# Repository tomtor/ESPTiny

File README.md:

# ATtiny84/16x4/x02 and ESP-01 (ESP8266) KiCad PCB and example code

## Usage

The main function of the ATtiny is acting as a battery friendly low power co-processor for the ESP.
A bit like the ULP low power co-processor of the ESP32, except with a lot more IO functions and program memory.

ATtiny and ESP combined use 22uA in sleep mode or even less when the ESP
is switched off by the ATtiny with CS.

Usable on breadboard (ATtiny84: 9 rows high, leaves 2 rows empty and ATtiny16x4: 8 rows high) OR stand alone.

3 PCB designs: ATtiny84 or ATtiny16x4 or ATtinyx02

All components / features are optional:

- ATtiny84 or ATtiny1604 / ATtiny1614 or ATtiny202 / ATtiny402
- ESP-01 (When not used the connections/space can be used for any other (I2C) device)
- LED with resistor
- MCP1700 low quiescent current regulator
- BAT85 diode for Solar Charging panel (see https://www.thethingsnetwork.org/labs/story/a-cheap-stm32-arduino-node/step/solar-power)
- Voltage divider for measuring battery voltage
- Decoupling capacitors
- I2C communication between ESP and ATtiny (with optional 4k7 pull-up)
- ATtiny can restart ESP by pulling ESP Reset low

## Example code

The ATtiny wakes up the ESP every 10 minutes by pulling RST low and sends a counter and the supply voltage to it.

### OTA for the ESP
OTA for ESP program updates is activated for 20s when the I2C communication fails.
This can be triggered by resetting the ESP by pulling the RST line low.
Because the ATtiny is most of the time sleeping
the I2C communication will fail.

There is a small chance that the ATtiny will reset the ESP during upload when the 10 minute interval is completed.
You can prevent this by pulling the ATtiny RST low when using OTA, or just upload again.

## Schemas

https://github.com/tomtor/ESPTiny/raw/master/ESPTiny.pdf

https://github.com/tomtor/ESPTiny/raw/master/ESPTiny1614.pdf

https://github.com/tomtor/ESPTiny/raw/master/ESPTiny402.pdf

## Credits

https://github.com/jdunmire/kicad-ESP8266

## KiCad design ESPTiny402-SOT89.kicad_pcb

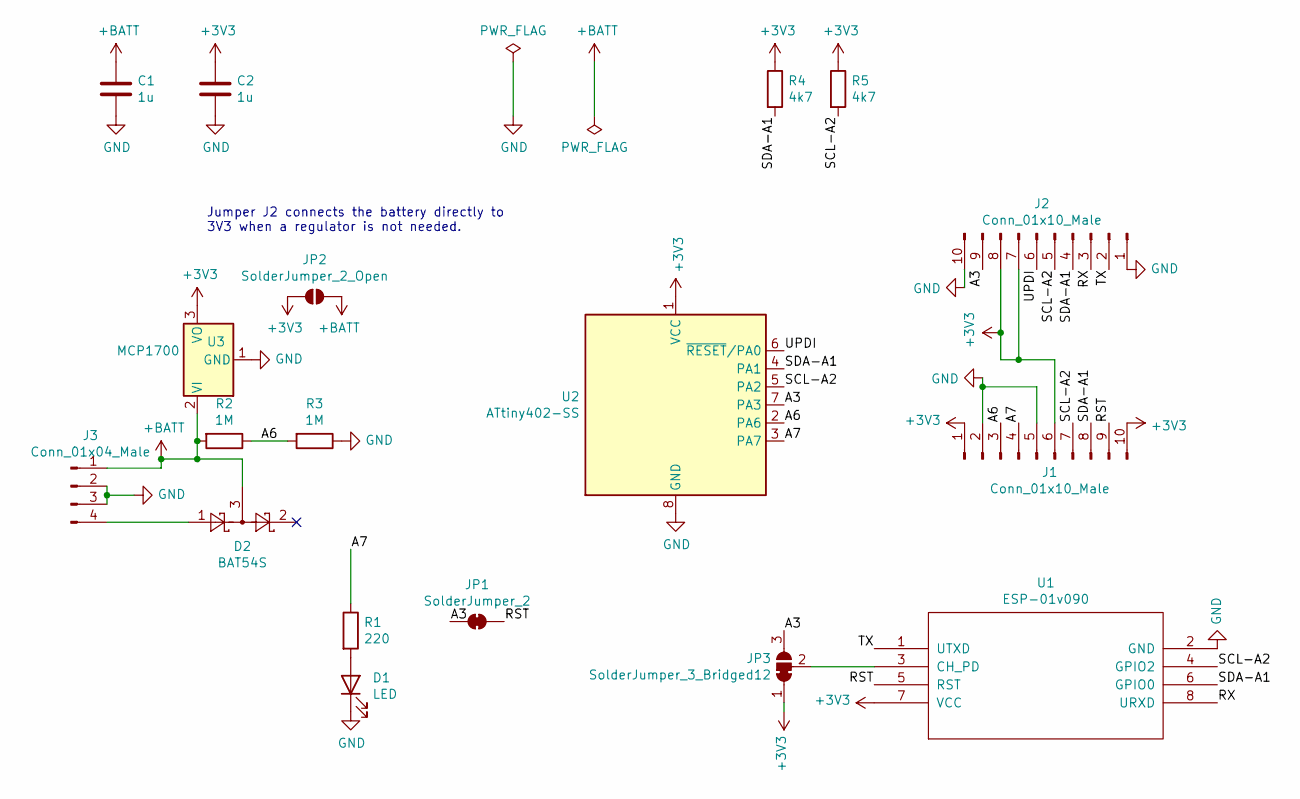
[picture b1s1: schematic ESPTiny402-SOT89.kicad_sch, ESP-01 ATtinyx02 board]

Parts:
C1, C2: 1u; C_1206_3216Metric
D1: LED; LED_1206_3216Metric
D2: BAT54S; SOT-23
J1, J2: Conn_01x10_Male; PinHeader_1x10_P2.54mm_Vertical
J3: Conn_01x04_Male; PinHeader_1x04_P2.54mm_Vertical
JP1: SolderJumper_2; SolderJumper-2_P1.3mm_Bridged_RoundedPad1.0x1.5mm
JP2: SolderJumper_2_Open; SolderJumper-2_P1.3mm_Open_Pad1.0x1.5mm
JP3: SolderJumper_3_Bridged12; SolderJumper-3_P1.3mm_Bridged12_RoundedPad1.0x1.5mm_NumberL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
R1: 220; R_1206_3216Metric
R2, R3: 1M; R_1206_3216Metric
R4, R5: 4k7; R_1206_3216Metric
U1: ESP-01v090; ESP-01
U2: ATtiny402-SS; SOIC-8_3.9x4.9mm_P1.27mm
U3: MCP1700; SOT-89-3

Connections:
+3V3: C2.1, J1.1, J1.6, J1.10, J2.7, J2.8, JP2.1 (A), JP3.1 (A), R4.1, R5.1, U1.7 (VCC), U2.1 (VCC), U3.3 (VO)
+BATT: C1.1, D2.3, J3.1, JP2.2 (B), R2.2, U3.2 (VI)
/A3: J2.9, JP1.1 (A), JP3.3 (B), U2.7 (PA3)
/A6: J1.3, R2.1, R3.2, U2.2 (PA6)
/A7: J1.4, R1.1, U2.3 (PA7)
/RST: J1.9, JP1.2 (B), U1.5 (RST)
/RX: J2.3, U1.8 (URXD)
/SCL-A2: J1.7, J2.5, R5.2, U1.4 (GPIO2), U2.5 (PA2)
/SDA-A1: J1.8, J2.4, R4.2, U1.6 (GPIO0), U2.4 (PA1)
/TX: J2.2, U1.1 (UTXD)
/UPDI: J2.6, U2.6 (~RESET/PA0)
GND: C1.2, C2.2, D1.1 (K), J1.2, J1.5, J2.1, J2.10, J3.2, J3.3, R3.1, U1.2 (GND), U2.8 (GND), U3.1 (GND)
unnamed: D1.2 (A), R1.2
unnamed: D2.1, J3.4
unnamed: JP3.2 (C), U1.3 (CH_PD)

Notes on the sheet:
Jumper J2 connects the battery directly to 3V3 when a regulator is not needed.

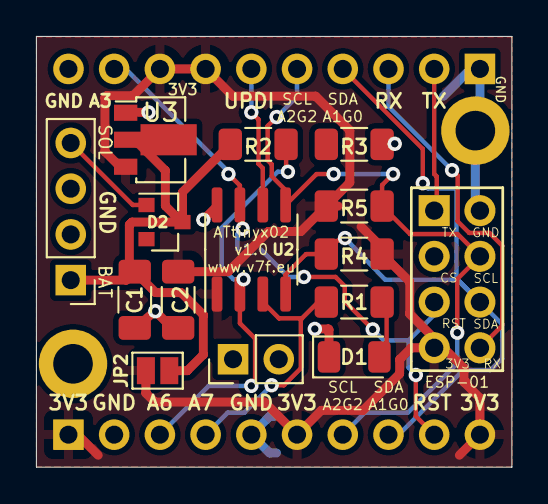
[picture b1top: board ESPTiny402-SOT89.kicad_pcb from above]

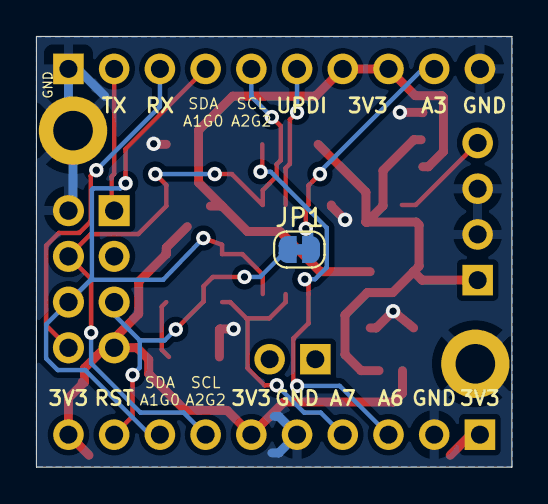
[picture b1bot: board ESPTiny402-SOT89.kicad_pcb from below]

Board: 2 copper layers, 26.4 x 23.9 mm, 17 parts (3 on the bottom side), 14 nets.

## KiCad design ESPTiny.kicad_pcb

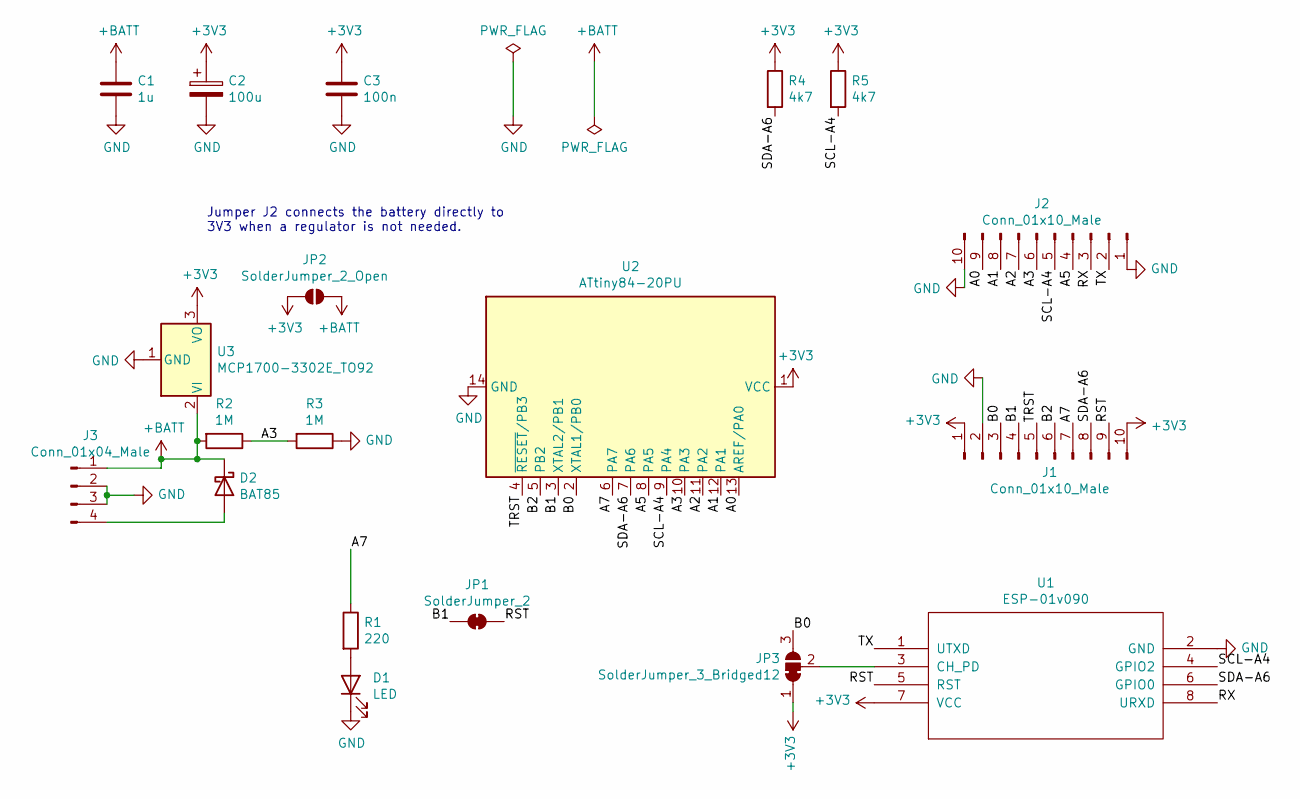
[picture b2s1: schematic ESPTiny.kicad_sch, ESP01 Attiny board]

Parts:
C1: 1u; C_Disc_D3.8mm_W2.6mm_P2.50mm
C2: 100u; CP_Radial_D5.0mm_P2.50mm
C3: 100n; C_Disc_D3.8mm_W2.6mm_P2.50mm
D1: LED; LED_D3.0mm
D2: BAT85; D_DO-35_SOD27_P2.54mm_Vertical_AnodeUp
J1, J2: Conn_01x10_Male; PinHeader_1x10_P2.54mm_Vertical
J3: Conn_01x04_Male; PinHeader_1x04_P2.54mm_Horizontal
JP1: SolderJumper_2; SolderJumper-2_P1.3mm_Bridged_RoundedPad1.0x1.5mm
JP2: SolderJumper_2_Open; SolderJumper-2_P1.3mm_Open_RoundedPad1.0x1.5mm
JP3: SolderJumper_3_Bridged12; SolderJumper-3_P1.3mm_Bridged12_RoundedPad1.0x1.5mm_NumberL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
R1: 220; R_Axial_DIN0207_L6.3mm_D2.5mm_P2.54mm_Vertical
R2, R3: 1M; R_Axial_DIN0207_L6.3mm_D2.5mm_P2.54mm_Vertical
R4, R5: 4k7; R_Axial_DIN0207_L6.3mm_D2.5mm_P2.54mm_Vertical
U1: ESP-01v090; ESP-01
U2: ATtiny84-20PU; DIP-14_W7.62mm
U3: MCP1700-3302E_TO92; TO-92_Inline

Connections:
+3V3: C2.1, C3.1, J1.1, J1.10, JP2.1 (A), JP3.1 (A), R4.1, R5.1, U1.7 (VCC), U2.1 (VCC), U3.3 (VO)
+BATT: C1.1, D2.1 (K), J3.1, JP2.2 (B), R2.2, U3.2 (VI)
/A0: J2.9, U2.13 (AREF/PA0)
/A1: J2.8, U2.12 (PA1)
/A2: J2.7, U2.11 (PA2)
/A3: J2.6, R2.1, R3.2, U2.10 (PA3)
/A5: J2.4, U2.8 (PA5)
/A7: J1.7, R1.1, U2.6 (PA7)
/B0: J1.3, JP3.3 (B), U2.2 (XTAL1/PB0)
/B1: J1.4, JP1.1 (A), U2.3 (XTAL2/PB1)
/B2: J1.6, U2.5 (PB2)
/RST: J1.9, JP1.2 (B), U1.5 (RST)
/RX: J2.3, U1.8 (URXD)
/SCL-A4: J2.5, R5.2, U1.4 (GPIO2), U2.9 (PA4)
/SDA-A6: J1.8, R4.2, U1.6 (GPIO0), U2.7 (PA6)
/TRST: J1.5, U2.4 (~RESET/PB3)
/TX: J2.2, U1.1 (UTXD)
GND: C1.2, C2.2, C3.2, D1.1 (K), J1.2, J2.1, J2.10, J3.2, J3.3, R3.1, U1.2 (GND), U2.14 (GND), U3.1 (GND)
unnamed: D1.2 (A), R1.2
unnamed: D2.2 (A), J3.4
unnamed: JP3.2 (C), U1.3 (CH_PD)

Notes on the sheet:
Jumper J2 connects the battery directly to 3V3 when a regulator is not needed.

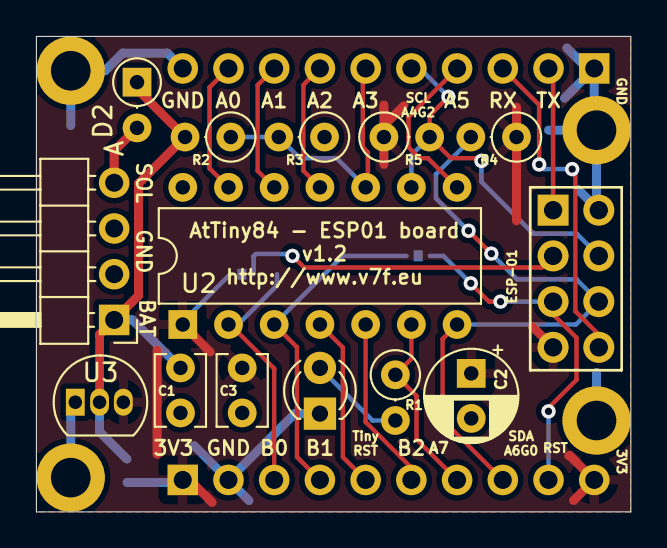
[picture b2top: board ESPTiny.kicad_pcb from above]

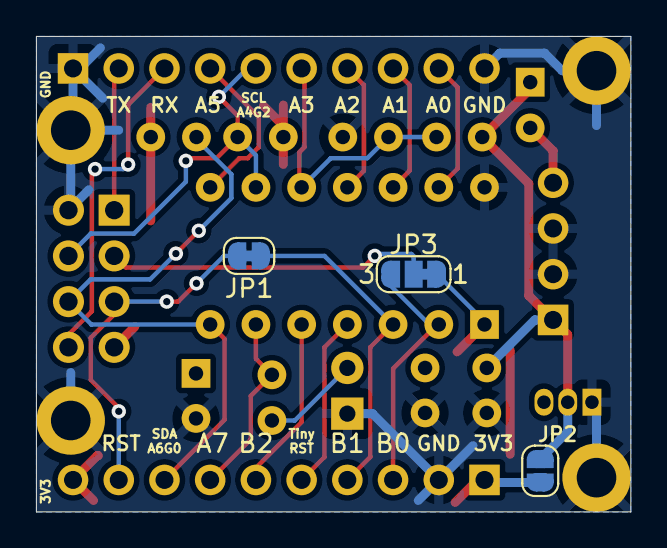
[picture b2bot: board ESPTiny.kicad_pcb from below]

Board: 2 copper layers, 33.0 x 26.4 mm, 19 parts (5 on the bottom side), 21 nets.

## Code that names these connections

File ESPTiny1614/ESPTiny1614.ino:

#define led       PIN_PA7
#define ON_TIME   3

// #define reset_ESP PIN_PB3
#define reset_ESP PIN_PA5

#define USE_BME  0
#define USE_ESP 0

#define USE_OSC 0

// Slowdown 2 sec every 24 hours:
// 24 * 3600 / 2 = 43200 ticks with 2 second interval in 24 hours.
// Adjustment is in steps of 2 seconds (a ticks increments the clock with 2 seconds).

//#define ADJUST 65535 // Slightly less than 1 second every 24 hours


#if USE_ESP || USE_BME
#include <Wire.h>
#endif

#include <avr/sleep.h>


#if USE_BME
#include <BME280I2C.h>

BME280I2C bme;
#endif

void RTC_init(void)
{
  /* Initialize RTC: */
  while (RTC.STATUS > 0)
  {
    ;                                   /* Wait for all register to be synchronized */
  }
#if USE_OSC
  RTC.CLKSEL = RTC_CLKSEL_INT32K_gc;    /* 32.768kHz Internal Ultra-Low-Power Oscillator (OSCULP32K) */
#else
  _PROTECTED_WRITE(CLKCTRL.XOSC32KCTRLA, 0x3);

  while (RTC.STATUS > 0) ;

  RTC.CLKSEL = RTC_CLKSEL_TOSC32K_gc;   /* 32.768kHz External Oscillator */
#endif

  RTC.PITINTCTRL = RTC_PI_bm;           /* PIT Interrupt: enabled */

  // For 2s overflow ticks while sleeping:
  RTC.INTCTRL = RTC_OVF_bm;
  
  RTC.CTRLA = RTC_PRESCALER_DIV1_gc | RTC_RUNSTDBY_bm | RTC_RTCEN_bm;
}


volatile uint16_t ticks;

ISR(RTC_PIT_vect)
{
  if (ticks)
    ticks--;
  RTC.PITINTFLAGS = RTC_PI_bm;          /* Clear interrupt flag by writing '1' (required) */
}


volatile uint8_t sec2s, hours, minutes; // 2s ticks

ISR(RTC_CNT_vect)
{
  static unsigned int adjust_ticks;

#if ADJUST > 0
  if (++adjust_ticks == ADJUST) {
    adjust_ticks = 0;
  } else {
#elif ADJUST < 0
  if (++adjust_ticks >= -ADJUST && sec2s == 0) {
    adjust_ticks = 0;
    sec2s = 4;
  } else {
#else
  {
#endif
    if (sec2s < 58)
      sec2s += 2;
    else {
      sec2s = 0;
      if (minutes < 59)
        minutes++;
      else {
        minutes = 0;
        if (hours < 23)
          hours++;
        else
          hours = 0;
      }  
    }
  }

  RTC.INTFLAGS = RTC_OVF_bm;          /* Clear interrupt flag by writing '1' (required) */
}


void sleepDelay(uint16_t n)
{
  uint8_t period;

#if 0
  if (n < 10) {
    period = RTC_PERIOD_CYC4_gc; // 1/8 ms
    ticks = (n << 3);
  } else
#endif
  if (n < 10) {
      period = RTC_PERIOD_CYC8_gc; // 1/4 ms
      ticks = (n << 2);
  } else if (n < 1000) {
      period = RTC_PERIOD_CYC64_gc; // 2 ms
      ticks = (n >> 1);
  } else if (n < 5000) {
      period = RTC_PERIOD_CYC1024_gc; // 32 ms
      ticks = (n >> 5);
  } else {
      period = RTC_PERIOD_CYC8192_gc; // 256 ms
      ticks = (n >> 8);
  }

  while (RTC.PITSTATUS & RTC_CTRLBUSY_bm)  // Wait for new settings to synchronize
    ;

  RTC.PITCTRLA = period | RTC_PITEN_bm;    // Enable PIT counter: enabled

  while (RTC.PITSTATUS & RTC_CTRLBUSY_bm)  // Wait for new settings to synchronize
    ;

  while (ticks)
    sleep_cpu();

  RTC.PITCTRLA = 0;    /* Disable PIT counter */
}

#if 1
unsigned int getBandgap ()
{
  analogReference(INTERNAL1V1);
  analogReference(VDD);
  analogRead(ADC_INTREF); // drop first
  return 0x400 * 1100UL / analogRead(ADC_INTREF);
} // end of getBandgap
#endif

#if 1
unsigned int getBattery ()
{
  analogReference(VDD);

  analogRead(PIN_PA3);
  unsigned int val = analogRead(PIN_PA3);

  // 3.3v regulator with voltage divider (820k/820k):
  const float Vref = 3300;
  const unsigned long scale = Vref*2;
  unsigned int results = scale * val / 0x400;

  return results;
} // end of getBattery
#endif


void testDelay(unsigned n, uint8_t l = led)
{
  digitalWrite(l, HIGH);
  sleepDelay(n);
  digitalWrite(l, LOW);
  sleepDelay(3);
}

void blinkN(uint8_t n, uint8_t l = led)
{
  for (uint8_t i = 0; i < n; i++) {
    digitalWrite(l, HIGH);
    sleepDelay(ON_TIME);
    digitalWrite(l, LOW);
    sleepDelay(700);
  }
}


void blinkDec(uint8_t d)
{
  blinkN(d / 10);
  sleepDelay(1500);
  blinkN(d % 10);
  sleepDelay(3000);
}


// the setup routine runs once when you press reset:
void setup() {
  RTC_init();                           /* Initialize the RTC timer */
  set_sleep_mode(SLEEP_MODE_STANDBY);
  sleep_enable();                       /* Enable sleep mode, but not going to sleep yet */

  pinMode(PIN_PA1, INPUT_PULLUP);
  pinMode(PIN_PA2, INPUT_PULLUP);
  pinMode(PIN_PA3, INPUT_PULLUP);
  pinMode(PIN_PA4, INPUT_PULLUP);
  pinMode(PIN_PA5, INPUT_PULLUP);
  pinMode(PIN_PA6, INPUT_PULLUP);
  pinMode(PIN_PA7, INPUT_PULLUP);
  pinMode(PIN_PB0, INPUT_PULLUP);
  pinMode(PIN_PB1, INPUT_PULLUP);
#if !USE_OSC
  pinMode(PIN_PB2, INPUT_PULLUP);
  pinMode(PIN_PB3, INPUT_PULLUP);
#endif

  pinMode(led, OUTPUT);

  for (byte i = 0; i < 3; i++) {
    blinkN(1, led);
  }

  sleepDelay(1000);
  for (int d= 1; d <= 10; d++)
    testDelay(d);
  sleepDelay(5000);
}


unsigned voltage;

volatile unsigned cnt;

#if USE_ESP
// function that executes whenever data is requested by master
// this function is registered as an event
void requestEvent() {
  Wire.write(cnt >> 8);
  Wire.write(cnt & 0xFF);
  Wire.write(voltage >> 8);
  Wire.write(voltage & 0xFF);

  ++cnt;
}
#endif


// the loop routine runs over and over again forever:TRLA = 0;
  // return 
void loop() {

  //delay(1);
  //unsigned int v = voltage = getBattery();
  unsigned int v = voltage = getBandgap();
  blinkDec((v + 50) / 100);

  blinkDec(minutes);

  sleepDelay(5000);
  while (sec2s != 0) {
    if (sec2s % 10 == 0 && sec2s <= 55) {
      blinkN(1);
      sleepDelay(9000);
    } else
      sleepDelay(100);
  }

#if USE_BME
  Wire.begin(1);                // join i2c bus with address #1
  bme.begin();
#if 0
  float temp(NAN), hum(NAN), pres(NAN);

  BME280::TempUnit tempUnit(BME280::TempUnit_Celsius);
  BME280::PresUnit presUnit(BME280::PresUnit_Pa);

  bme.read(pres, temp, hum, tempUnit, presUnit);
#else
  static float oldtemp;
  float temp;
  if ((temp = bme.temp()) == oldtemp)
    return;
  oldtemp = temp;
#endif
#endif

#if USE_ESP
  digitalWrite(reset_ESP, LOW);
  pinMode(reset_ESP, OUTPUT);
  sleepDelay(32);
  pinMode(reset_ESP, INPUT_PULLUP);

  sleepDelay(3000);

  auto startcnt = cnt;

  Wire.begin(1);                // join i2c bus with address #1
  Wire.onRequest(requestEvent); // register event

  auto end = millis() + 4000;
  while (cnt == startcnt && millis() < end)
    ;
  delay(200);
  Wire.end();
#endif
}

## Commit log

2021-06-19 Start on design of combi ESP-01 Attiny84 board
2021-06-19 Add footprints
2021-06-27 Without power divider
2021-06-27 With power divider
2021-06-27 v1.0?
2021-06-27 Add upper fills
2021-06-27 Fix priority 3V3 zone
2021-06-27 Move PWR labels in corner
2021-06-27 README
2021-06-27 README.md
2021-06-27 PDF and 3D
2021-06-28 Fix ESP CH_PD to 3V3
2021-06-28 Copper fill
2021-06-28 Copper fill smaller clearance
2021-06-28 Copper fill smaller clearance: 0.27
2021-06-29 Copper fill clearance: 0.3 width: 0.2
2021-06-29 Clean up
2021-06-29 Better GND plane
2021-06-29 D2 silk
2021-06-29 3D PNG
2021-06-30 Add 4k7 pull up for I2C
2021-06-30 extra GND trace
2021-06-30 SVG schema
2021-06-30 SVG schema rotate
2021-07-01 Add RST jumper
2021-07-01 Add example Arduino sources
2021-07-01 0.1 production
2021-07-01 Improve examples
2021-07-02 Update schema prints
2021-07-02 Update 3D
2021-07-03 Add OTA upload
2021-07-03 Add to README
2021-07-03 SVG orientation
2021-07-03 Cleanup and disable pin change interrupt
2021-07-03 600s per iteration
2021-07-04 Disable wakeup from pin change and add ESP voltage guard
2021-07-04 Disable wakeup from pin change and USI
2021-07-04 attiny watch voltage
2021-07-05 cleanup some tiny code
2021-07-06 Add local ESP lib
2021-07-06 Add ESP library credit
2021-07-06 1.1 repositioning
2021-07-06 Refresh 3D png
2021-07-07 cleanup tracks
2021-07-08 Rev 1.2 Power bridge, layout
2021-07-08 Add schema SVG/PDF and 3D PNG
2021-07-08 Rename schema to ESPTiny
2021-07-08 cleanup
2021-07-08 Tune pin labels
2021-07-08 Refresh 3D image
2021-07-08 Add comment for J2 jumper
2021-07-09 Replace tantalum C with electrolytic
2021-07-09 Battery voltage divider from A1 to A3
2021-07-10 Replace TinyWire with default Wire library
2021-07-12 Add CH_PD ESP01 jumper
2021-07-12 Update schema PDF/SVG
2021-07-13 note about pin change
2021-07-14 Update README for AtTiny16x4
2021-07-14 Add AtTiny16x4 PCB
2021-07-14 Update README: Use any I2C device instead of ESP01
2021-07-14 Update silk screen
2021-07-14 Update 3V3 plane
2021-07-14 Add thermal isolation for front solder jumper
2021-07-15 Silkscreen update
2021-07-15 consistent ATtiny spelling
2021-07-15 Add empty PCB images
2021-07-15 Silk screen update
2021-07-15 Update 1614 front silkscreen
2021-07-15 New 3D 1614 component image
2021-07-16 Change solder jumper footprint with thermal insulation
2021-07-16 revert pin comment
2021-07-18 Fix RST to A1
2021-07-18 Fix RST to B3
2021-07-19 Fix 4Mhz timing
2021-07-19 Update 16x2 PCB silk, 1.0 production
2021-07-26 Start on 402 SMD PCB
2021-07-29 Add ESPTinyx02
2021-07-29 Update 4x2 and README
2021-07-29 C3 -> C2 rename
2021-07-29 Remove some support 3V3 tracks
2021-07-29 Better power routing
2021-07-29 Fix silk screen back
2021-07-29 Fix silk screens
2021-07-29 Improve routing
2021-07-29 Update images
2021-07-29 Update silk screen attiny84
2021-07-30 Minor layout changes
2021-07-31 Remove .net files
2021-07-31 Led to 1206 size
2021-07-31 Minor routing updates
2021-07-31 Larger silk text
2021-07-31 Minor silk updates
2021-08-01 SOT89 version
2021-08-01 SOT89 version reorder
2021-08-02 SOT89 add TH position
2021-08-02 Update 402 layout and images
2021-08-02 Update 402 layout
2021-08-10 A1 voltage measurement
2021-08-10 production 402 SOT89
2021-08-12 Start on 1614 code
2021-08-13 1614 rtc update
2021-08-14 Improved sleepDelay for attiny1614
2021-08-15 Add BME280 example code
2021-08-21 Fix timing
2021-08-23 Fix voltage calculation (use unsigned long)
2021-08-24 Version 2.0 Add crystal and move ESP reset to other pin
2021-08-24 Silk screen
2021-08-24 Update layout of MCP1700 and power pins
2021-08-24 New images
2021-08-24 Breadboard size corrected
2021-09-01 Add ATtiny402 sketch
2021-09-03 Add RTC clock code (prepare for crystal)
2021-09-04 Blink Decimal code and show HH:MM:SS uptime
2021-09-05 Fix interrupt code
2021-09-10 Update status every minute
2021-09-19 Add capacitors to 32768 crystal
2021-09-20 Better silk 1614 and improve battery code
2021-09-20 Better silk 1614
2021-10-13 Adjust clock and guard against low battery
2022-01-11 Create LICENSE
2025-03-06 1614
2025-03-07 ESP1614 timing test
2025-03-07 ESP1614 fix bandgap
2025-03-13 Minor cosmetic cleanups
2025-03-17 use RTC compare instead of PIT
2025-03-18 Cleanup comments
2025-03-18 More accurate timing
2025-03-18 Added some test code (event and CCL)
2025-03-18 Exact calculation of ms!
2025-03-18 adjust millis() while sleeping
2025-03-19 support shorter RTC periods (eg 1000ms instead of 2000ms)
2025-03-19 Debug version
2025-03-19 Fix ticks interrupt handling
2025-03-19 Missed var declaration
2025-03-19 remove wrong nudge
2025-03-25 interim
2025-03-25 Test sleep timer code
2025-03-27 Tested timing
2025-03-31 Alternative sleepDelay() implementation
2025-04-01 clean time test
